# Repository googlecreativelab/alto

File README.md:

<table>
  <tr>
    <td>
      This project is no longer actively maintained by the Google Creative Lab but remains here in a read-only Archive mode so that it can continue to assist developers that may find the examples helpful. We aren’t able to address all pull requests or bug reports but outstanding issues will remain in read-only mode for reference purposes. Also, please note that some of the dependencies may not be up to date and there hasn’t been any QA done in a while so your mileage may vary.
      <br><br>
      For more details on how Archiving affects Github repositories see <a href="https://docs.github.com/en/github/creating-cloning-and-archiving-repositories/about-archiving-repositories">this documentation </a>.
      <br><br>
      <b>We welcome users to fork this repository</b> should there be more useful, community-driven efforts that can help continue what this project began.
    </td>
  </tr>
</table>

# Alto - a little teachable object<br>
<br>

Say hello to Alto, a little teachable object! Alto is designed to demonstrate the most basic aspects of machine learning (ML) by building a machine you can teach yourself. Alto uses the [Coral USB Accelerator](https://coral.ai/products/accelerator/) and Raspberry Pi to help show how you can easily add machine learning to your next hardware project.

This repository contains all of the instructions and files required to build an Alto of your own from scratch. Best of all, Alto is completely open source! Anyone can fork the code, schematics, and case designs to create a little teachable object of their own.

To find out more about what else you can do with the Edge TPU in the USB Accelerator, and get inspiration for your own projects, head to [Coral's Examples page](https://coral.ai/examples/).

<br>
<br>
## What you’ll find in this document

This document has five chapters:

-  **[User guide](#User-guide)** -
Explaining Alto’s interface and the ways Alto can be used.

-  **[Make your own Alto](#Make-your-own-Alto)** -
A visual guide to constructing your own Alto, covering setting up the software, soldering your circuitry and constructing Alto’s cardboard body.

- **[Experiment with Alto](#Experiment-with-Alto)** -
A set of simple experiments to help understand how Alto works, and how you can use Alto to introduce some of the basic concepts of machine learning to others.

- **[Remixing Alto](#Remixing-Alto-for-your-projects)** -
A brief introduction to how you can hack your Alto to look and behave differently to fit your own application.

- **[Technical overview](#Technical-Overview)** -
A more detailed overview of Alto’s software and electronics and how they function.<br>
<br>

## User guide

### Machine learning at its simplest

Alto has a camera on its front, and an arm and button on each side. Alto uses the camera to observe the world around it. The buttons are used to start learning, and Alto will point with its arm when it sees something it has learned to recognise. 

<br>
<br>

Alto can learn two classes of things. When Alto recognises one of them, it will point with its corresponding arm. Alto demonstrates machine learning at its most basic level: what you teach it to recognise is up to you!

<br>
<br>

### Teaching Alto

To teach Alto to recognise an object, place the object in front of it, and press one of the buttons on the side. As Alto takes images to learn about the object, its arm will slowly raise. When Alto’s arm is stretched out horizontally, the learning process has finished. Now, when the same object is placed in front of it, Alto will point at the object.

The more you teach Alto about the same object, the better it will become at recognising that thing. You can teach Alto as many times as you like! Try teaching Alto more about an object by rotating the object to show different angles and place it at various distances, pressing the same button each time.

It's important to try and balance the amount of learning that Alto does on each side. If it learns about one object 5 times, but only once about another, then it is likely to be much better at recognising the one that it has seen more often.

<br>
<br>
### Recognising objects

Start by teaching Alto to recognise a different object for each arm, for example, to teach Alto the difference between types of fruit, teach it about a red apple on one side, and a banana on the other. 

<br>
<br>
### Recognising classes

Beyond recognising individual objects, you can teach Alto to recognise classes of objects. Building on what it has learned about red apples, could you teach it to recognise red objects in general, rather than just apples? Once Alto has learned to recognise two classes, can it correctly recognise a new red object that it hasn’t seen before?

<br>
<br>
### Forgetting

If you want to teach Alto something new, you can clear its memory by holding down both buttons simultaneously for 3 seconds. This will erase everything Alto was taught on both sides, and can’t be undone.

To learn about any of these processes in more detail, take a look at the [Experiment with Alto](#experiment-with-Alto) section below.

<br>
<br>
## Make your own Alto

The following steps will guide you through the process of assembling your own Alto: setting up the Raspberry Pi, soldering the electronics, and assembling a case to house all the components. To read a more detailed explanation of each step, click on the links in each section to go to the individual instruction pages. 

<br>
<br>
### 1.0: [Set up the software](1.0-Set-up-the-software.md)

The first step is to setup the software environment for Alto, and then load the Python code that makes Alto function. The Software & OS section outlines the process in full, starting with setting up the Raspberry Pi Zero, flashing the SD card and installing the Alto application software.

<br>
<br>
### 2.0: [Build the electronics](2.0-Build-the-electronics.md)

The electronics for Alto have been designed to be as simple and hackable as possible. You only need a few common components and basic soldering skills to assemble everything. A full step-by-step guide, with schematics and a bill of materials, is included in the Electronics directory in this repository.

<br>
<br>
### 3.1: [Making the electronics casing](3.1-Making-the-electronics-casing.md)

The inner structure of Alto is made from folded cardboard, and held together with staples. All the components of Alto are held in this structure: the servos, LEDs, camera, and the internal electronics package are all mounted in the cardboard layers.

To begin, you will need to print out the [PDF template](casing/alto-paper-templates.pdf) and stick it to your materials. This will be your guide for cutting the cardboard into the correct shape. All the labels are printed on the template itself.

You can accomplish this step using hand tools (e.g. a craft knife) which will take around 45 minutes, or a laser cutter if you have access to one, which will be significantly quicker.

For more detailed instructions on this stage of constructing your Alto, refer to the [electronics casing](3.1-Making-the-electronics-casing.md) instructions.

<br>
<br>
### 3.2: [Making Alto's outer casing](3.2-Making-altos-outer-shell.md)

The outer structure of Alto is made from card, and is designed to fit around and fold into the seams of Alto’s inner structure. The process is similar to before, outlined in full detail on the [outer](https://github.com/googlecreativelab/alto/blob/master/3.2-Making-altos-outer-shell.md) case build directory.

The white card makes up most of Alto’s outer structure, and hides some of its components and electronics. We provide printable coloured card accessories that highlight the yellow eye (camera), the red ears (buttons) and the blue arms (servo motor arms).

You can also customise the visual style at this stage to make your Alto unique!

<br>
<br>
### 4.0: [Teach!](4.0-experiments-with-alto.md)

You should now have a completed Alto unit – the next stage is to teach it!

Grab some objects, plug Alto into a power source, and start exploring what you can teach Alto to recognise. If you need a bit of inspiration to get going, take a look at the Experimenting with Alto section below.

<br>
<br>
## [Experiment with Alto](4.0-experiments-with-alto.md)

Alto is a great way to understand the basics of machine learning. This section contains a number of experiments to help understand how Alto works, and introduce the basics of machine learning to others.

Covering aspects from simple object recognition, to introducing k-nearest neighbor (kNN) algorithms, these experiments give practical ways to bring the concepts behind Alto to life. Head to the [Experiments with Alto](4.0-experiments-with-alto.md) page to read on.

<br>
<br>
## [Remixing Alto for your projects](5.0-remixing-alto.md)

All the hardware and software for Alto was created with hacking and remixing in mind: the case design can be made from different materials, or refactored entirely; the electronics can be adapted to use whatever components you have available; the servos can be substituted for any type of actuator; and the software is written in a high level language (Python) that is easy to modify. 

Here are just some of the ways you can hack your own Alto:

<br>
<br>
### Hacking the [software](5.0-remixing-alto.md#hacking-altos-software)
Small tweaks to the existing code can be made to change Alto’s confidence level or behaviours.

<br>
<br>
### Hacking the [hardware](5.0-remixing-alto.md#hacking-altos-hardware)

Go beyond servos, to explore new ways for Alto to show its recognised something.

<br>
<br>
### Hacking the [casing](5.0-remixing-alto.md#hacking-altos-casing)

The casing for Alto can easily be changed to fit whatever application you might have in mind. Whether that’s simple aesthetic changes to modify Alto’s look, or changes to the design of the arms or body that might let Alto do new things. 

<br>
<br>
Hacking Alto is a great step towards building your own machine learning projects. If you come up with anything cool using the Coral USB Accelerator, show us! Submit your machine learning experiment to the Experiments with Google platform [here](https://experiments.withgoogle.com/submit).

## Technical Overview

There are three main elements to Alto: a Raspberry Pi Zero single-board computer with a camera attachment; a [Coral USB Accelerator](https://coral.ai/products/accelerator/) for accelerating on-device machine learning; and some simple electronics for its user interface.<br>
<br>

### OS & compute

The Raspberry Pi Zero runs Raspberry Pi OS. It is responsible for interfacing with the user’s connected hardware (connected via GPIO), the camera module, and the Coral Edge TPU (connected via USB). The OS starts automatically, and acts as host for the software application that runs Alto. 

The system accelerates all ML inferencing (and some of the learning) by delegating ML graph execution to the Edge TPU on the Coral USB Accelerator. The Edge TPU is a machine learning coprocessor that enables low-powered computers like the Raspberry Pi to run advanced ML workloads at a much greater level of performance than if they were run on CPU. All of the ML tasks performed by Alto are done on-device (offline) using the Edge TPU.

Although the Coral software for the Edge TPU does not officially support the Raspberry Pi Zero (because it has an ARMv6 chipset, but Coral officially requires ARMv8), the [Coral software for the Edge TPU Runtime](https://github.com/google-coral/libedgetpu) is open sourced and has been successfully [compiled for the Raspberry Pi Zero](https://github.com/google-coral/edgetpu-platforms).

You can find out more about Coral and the Edge TPU hardware on the [Coral website](https://coral.ai/products/).<br>
<br>

### Software

The Alto software application is written in Python. It receives input from the Raspberry Pi camera module, prepares it for classification by the Edge TPU module, and interfaces with the electronics interface. The application uses a k-nearest neighbor classifier model (k-NN) to identify the proximity of a given image to others in its learned dataset.

When Alto is learning, it calculates the embedding of the incoming data from the image sensor in its model and assigns it a label - in the case of Alto, this label is either its left or right arm. When Alto is in recognition mode, the embeddings of data frames from the image sensor are determined and their proximity to other known embeddings is calculated; if these are within a certain distance of a labelled embedding, then Alto has recognised something, and will point at it with its corresponding arm.<br>
<br>

### Electronics

The electronics for Alto are designed to be as flexible and hackable as possible. It is based around a single through-hole prototyping board which can be assembled easily by hand. This board connects to the GPIO pins of the Raspberry Pi Zero, and breaks out headers for the other component parts of Alto: two servos, two buttons, and one LED.

Each of these items are common and easy to get, or you might even have them in your hacking space already. Alternatively, they can easily be substituted for other parts, for example if you have different servos or LEDs available. The design and Bill of Materials (BOM) includes a prefabricated USB breakout board, which includes a discrete power regulation circuit that will ensure smooth delivery of adequate power to Alto during normal operation.

You can find more information about the electronics in the [electronics](2.0-Build-the-electronics.md) directory, and the bill of materials is available [here](electronics/alto-bom.xlsx) as a downloadable spreadsheet.<br>
<br>

## Notes

This is a collaborative effort between Google Creative Lab and our partners at [RRD Labs](https://github.com/dgym). This is not an official Google product.

We encourage open sourcing projects as a way of learning from each other. Please respect our and other creators’ rights, including copyright and trademark rights when present when sharing these works and creating derivative work. If you want more info on Google's policy, you can find it [here](https://www.google.com/permissions/). To contribute to the project, please refer to the [contributing](CONTRIBUTING.md) document in this repository.

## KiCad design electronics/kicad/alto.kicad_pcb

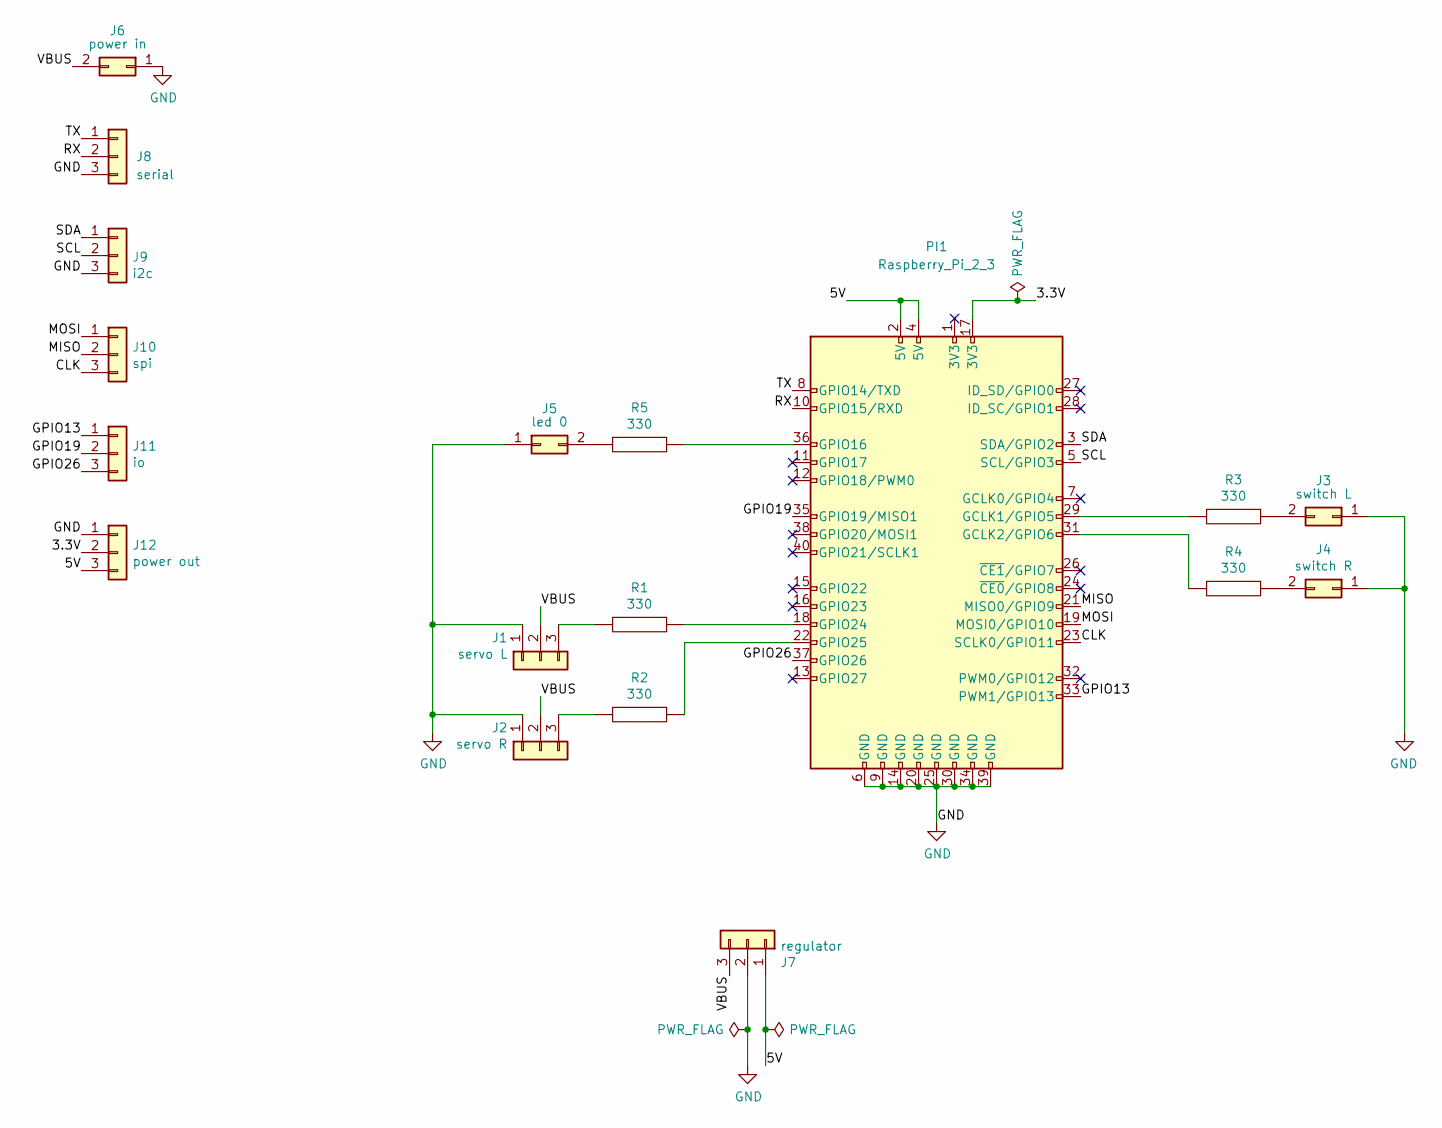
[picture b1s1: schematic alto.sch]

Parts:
J1: servo L; Pin_Header_Straight_1x03_Pitch2.54mm
J2: servo R; Pin_Header_Straight_1x03_Pitch2.54mm
J3: switch L; Pin_Header_Straight_1x02_Pitch2.54mm
J4: switch R; Pin_Header_Straight_1x02_Pitch2.54mm
J5: led 0; LED_D5.0mm
J6: power in; Pin_Header_Straight_1x02_Pitch2.54mm
J7: regulator; Pin_Header_Straight_1x03_Pitch2.54mm
J8: serial; Pin_Header_Straight_1x03_Pitch2.54mm
J9: i2c; Pin_Header_Straight_1x03_Pitch2.54mm
J10: spi; Pin_Header_Straight_1x03_Pitch2.54mm
J11: io; Pin_Header_Straight_1x03_Pitch2.54mm
J12: power out; Pin_Header_Straight_1x03_Pitch2.54mm
PI1: Raspberry_Pi_2_3; Socket_Strip_Straight_2x20_Pitch2.54mm
R1, R2, R3, R4, R5: 330; Resistor_SMD+THTuniversal_0805to1206_RM10_HandSoldering

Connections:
/3.3V: J12.2, PI1.17 (3V3)
/5V: J7.1, J12.3, PI1.2 (5V), PI1.4 (5V)
/CLK: J10.3, PI1.23 (SCLK0/GPIO11)
/GPIO13: J11.1, PI1.33 (PWM1/GPIO13)
/GPIO19: J11.2, PI1.35 (GPIO19/MISO1)
/GPIO26: J11.3, PI1.37 (GPIO26)
/MISO: J10.2, PI1.21 (MISO0/GPIO9)
/MOSI: J10.1, PI1.19 (MOSI0/GPIO10)
/RX: J8.2, PI1.10 (GPIO15/RXD)
/SCL: J9.2, PI1.5 (SCL/GPIO3)
/SDA: J9.1, PI1.3 (SDA/GPIO2)
/TX: J8.1, PI1.8 (GPIO14/TXD)
/VBUS: J1.2, J2.2, J6.2, J7.3
GND: J1.1, J2.1, J3.1, J4.1, J5.1, J6.1, J7.2, J8.3, J9.3, J12.1, PI1.6 (GND), PI1.9 (GND), PI1.14 (GND), PI1.20 (GND), PI1.25 (GND), PI1.30 (GND), PI1.34 (GND), PI1.39 (GND)
unnamed: J1.3, R1.1
unnamed: J2.3, R2.1
unnamed: J3.2, R3.1
unnamed: J4.2, R4.1
unnamed: J5.2, R5.1
unnamed: PI1.18 (GPIO24), R1.2
unnamed: PI1.22 (GPIO25), R2.2
unnamed: PI1.29 (GCLK1/GPIO5), R3.2
unnamed: PI1.31 (GCLK2/GPIO6), R4.2
unnamed: PI1.36 (GPIO16), R5.2

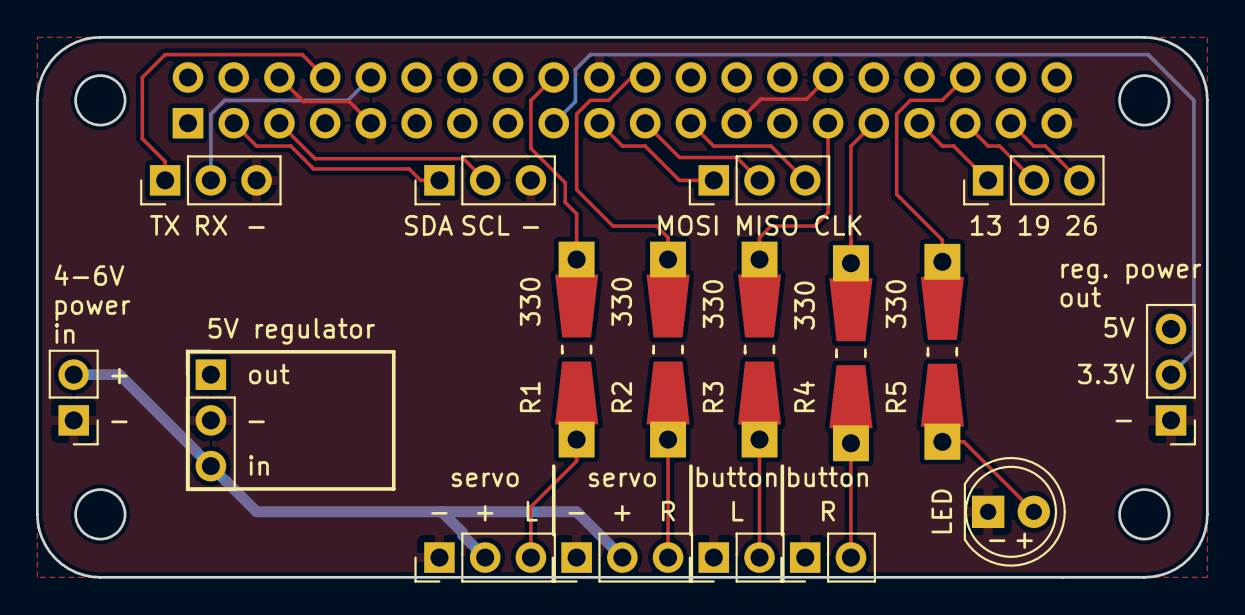
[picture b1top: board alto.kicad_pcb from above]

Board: 2 copper layers, 65.0 x 30.0 mm, 18 parts (1 on the bottom side), 24 nets.

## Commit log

2021-02-10 Initial sync commit
2021-07-04 Update 1.0-Set-up-the-software.md
    Add link to repository and uncapitalise filenames.
2021-09-05 modified naming convention of alto.py
2025-08-18 Update README.md
    Archiving repo
